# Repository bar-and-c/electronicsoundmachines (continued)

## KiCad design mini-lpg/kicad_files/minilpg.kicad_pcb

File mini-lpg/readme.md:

# Mini-LPG

General disclaimer: I have never used a real LPG, but I understand it is a bit more complex than this circuit. The control mechanism, as I understand it, is similar, though – using an optocoupler (often called Vactrol, after a common type). 

An optocoupler of this kind is an enclosed LED and a light dependent resistor (LDR): the more light from the LED, the lower the resistance. So, in this filter, the control voltage is used to make the LED shine, and the LDR is used in a simple low pass filter circuit. Voila – a simple voltage controlled filter. 

In revision A of this circuit I added (almost) as many extra add-ons I could think of – and left room for further, not yet thought of, modifications. In hindsight, I think I could have held back a bit: the distortion is weak (to my defence, it sounded much better on the breadboard – no idea what changed from that), possibly depending on what kind of signal you put through it; the band pass mode is not useless, but not extremely useful as it cuts a _lot_ of low end; the mod area and jumpers are a good idea in general, but on this particular device, maybe not... 

Annoyingly enough, one of the things I thought of but didn't include, a capacitor in series with the CV input to get a decay (given a gate signal as input), is something I have on similar cicuits and find really useful when lacking envelope generators. So I should have included that and omitted other stuff. Well well.

Most importantly, though: for some reason, the range is surprisingly narrow. Theorethically I had imagined that 0-12 volts would result in a filter going from completely silent to wide open, but in reality, the effective CV range is about 1.4 - 2.0 volts, or so. I don't know why. Could be that particular type of optocoupler, or something in the rest of my (mostly home built) synthesizer, or something in the overall design of the circuit, but there you go. 

So, that is good to know if you are considering building this. 

Having said that, I still think it brings a bit of value, at least if you have a tiny tiny modular like I do (at the time of building this, I have three oscillators, an eight step sequencer, a mixer module with two mixers in it, and two other passive LPGs similar to this one).

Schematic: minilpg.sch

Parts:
C1: 22nF; C_Rect_L7.2mm_W2.5mm_P5.00mm_FKS2_FKP2_MKS2_MKP2
D1: LED; LED_D3.0mm
D2: 1N4148; D_DO-35_SOD27_P7.62mm_Horizontal
D3: BAT43; D_DO-35_SOD27_P7.62mm_Horizontal
J1: CV; Switchcraft_35RAPC2AV_3_5_mm_jack
J2: IN; Switchcraft_35RAPC2AV_3_5_mm_jack
J3: OUT; Switchcraft_35RAPC2AV_3_5_mm_jack
JP1: MOD_CV; Pin_Header_Straight_1x02_Pitch2.54mm
JP2: MOD_IN; Pin_Header_Straight_1x02_Pitch2.54mm
JP3: MOD_MID; Pin_Header_Straight_1x02_Pitch2.54mm
JP4: MOD_OUT; Pin_Header_Straight_1x02_Pitch2.54mm
L1: 47mH; L_Radial_D12.0mm_P5.00mm_Fastron_11P
R1: 470; R_Axial_DIN0207_L6.3mm_D2.5mm_P7.62mm_Horizontal
R2: 270; R_Axial_DIN0207_L6.3mm_D2.5mm_P7.62mm_Horizontal
R3: 10k; R_Axial_DIN0207_L6.3mm_D2.5mm_P7.62mm_Horizontal
RV1: 50k; Potentiometer_Alps_RK09K_Horizontal
SW1: LP/BP; Switch-SPDT-angled
SW2: LPG/VCA; Switch-SPDT-angled
SW3: MINIDIST; Switch-SPDT-angled
U1: NSL-32; Optoisolator_NSL-32

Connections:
GND: D1.1, D2.2, J1.2, J2.2, J3.2, SW2.2 (B), SW3.2 (B), U1.2 (K)
unnamed: C1.1, D3.1 (K), JP3.2, JP4.1, L1.1, R3.2
unnamed: C1.2, SW1.2 (B), SW2.1 (A)
unnamed: D1.2, R1.1
unnamed: D2.1, R2.1, U1.1 (A)
unnamed: D3.2 (A), SW3.3 (C)
unnamed: J1.1, JP1.1, R1.2
unnamed: J2.1, JP2.2
unnamed: J3.1, JP4.2
unnamed: JP1.2, R2.2
unnamed: JP2.1, RV1.2, RV1.3
unnamed: JP3.1, U1.3 (R)
unnamed: L1.2, SW1.3 (C)
unnamed: R3.1, SW2.3 (C)
unnamed: RV1.1, U1.4 (R)

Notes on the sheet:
NOTE: The resistor values on the CV side are chosen to match the LEDs in the kit; 40 mA for the optocoupler and 20 mA for the LED. If you change these components, make sure the resistors match. Similarly, the components on the audio side are chosen to work OK with the optocoupler I chose (it has 50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
MODS: - The dist connaisseur mod: put a diode (Schottky or Germanium, since those have lower voltage drop => less loss) directly after the audio in jack, for another type of dist. - The filter mod: Put another capacitor (of significantly higher (or lower) value) instead of the VCA resistor (R3), fo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
Mini LPG
Mini LPG
September 8, 2018

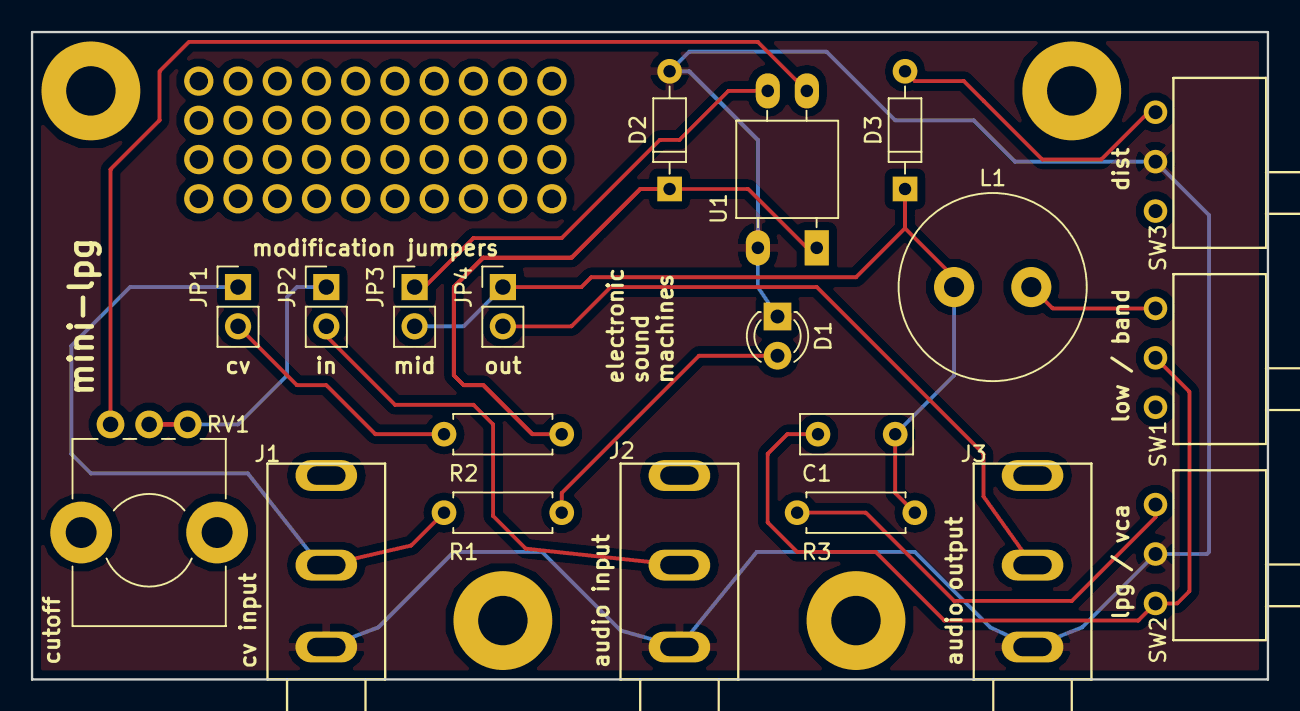
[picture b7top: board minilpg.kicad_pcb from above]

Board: 2 copper layers, 80.0 x 41.9 mm, 20 parts (0 on the bottom side), 15 nets.

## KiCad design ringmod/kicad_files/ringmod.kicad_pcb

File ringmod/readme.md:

# Ring modulator

This is just a textbook example of a ring modulator (see Wikipedia for reference). Given two input signals, the input and the carrier, as I understand it the output is the sum and difference frequencies (in an ideal circuit the input frequencies should not be in the output at all). 

In a more non-mathematical language: given two inputs, the input and the carrier, the output can be a bit unpredictable and often rather disharmonic. It can be used to create bell like sounds, robotic voices, or even quite pleasant sounds (if the input frequencies are carefully selected). 

It is super easy to build, and easy to use as it requires no power supply, just two input signals (just not too low in amplitude, use a pre-amplifier if needed).

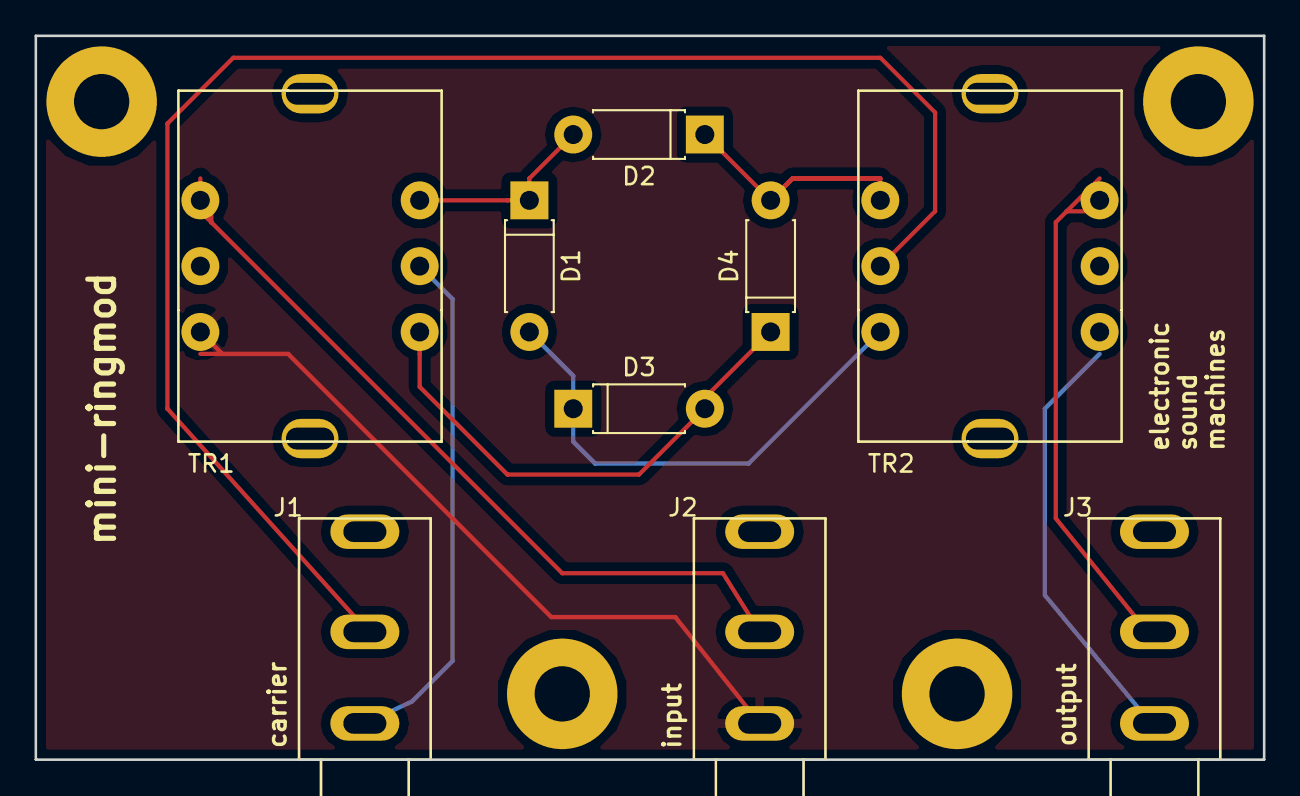
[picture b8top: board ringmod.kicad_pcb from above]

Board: 2 copper layers, 71.1 x 41.9 mm, 9 parts (0 on the bottom side), 10 nets.

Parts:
D1, D2, D3, D4: BAT43; D_DO-41_SOD81_P7.62mm_Horizontal
J1: CARRIER; Switchcraft_35RAPC2AV_3_5_mm_jack
J2: IN; Switchcraft_35RAPC2AV_3_5_mm_jack
J3: OUT; Switchcraft_35RAPC2AV_3_5_mm_jack
TR1, TR2: 42TM018; Transformer-42TM018

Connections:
unnamed: D1.1, D2.2, TR1.6
unnamed: D1.2, D3.1, TR2.3
unnamed: D2.1, D4.2, TR2.1
unnamed: D3.2, D4.1, TR1.4
unnamed: J1.1, TR2.2
unnamed: J1.2, TR1.5
unnamed: J2.1, TR1.1
unnamed: J2.2, TR1.3
unnamed: J3.1, TR2.6
unnamed: J3.2, TR2.4

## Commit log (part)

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2018-02-21 Add initial Jekyll site
2018-02-21 The first version with some content
2018-02-21 Add layout from minima theme, to override
    And overriding a bit already.
2018-02-21 Make image smaller
2018-02-22 Add Gemfile.lock to repo
2018-02-22 Add minima assets in feeble attempt to make it work
2018-02-22 Copy stuff from working jekyll site
2018-02-22 clean up config
2018-02-22 Add a lot of info, and enhanced image
2018-02-22 Remove repetitive phrase
2018-02-22 Remove typo in URL
    Trying to get the form in English. Good luck with that!
2018-02-22 Adjust the image text a tad south
2018-02-23 Add and reorganize content
2018-02-23 Add more on learning
2018-02-23 Update about language
2018-02-23 Changed wording
2018-02-23 Express that spending time on experiments is not mandatory
2018-02-26 Change name from 'guitar' to 'effect'
2018-03-14 Update with info about gender balance
2018-03-14 Add more info on gender balance, removing Google Form
2018-03-16 Add initial documentation
    Still a long way to go, with adding schematics, and maybe photos.
2018-03-16 Add custom library with power pins
    4017 and 40106 didn't have explicit power pins, which drove me insane,
    so I made my own copies.
    4017 has its old pins, but no longer invisible, and 40106 has a new
    part (G) that holds power pins.
    Help: https://www.youtube.com/watch?v=-1WVtuzKmz8
2018-03-16 Add schematic as PDF, rev A
2018-03-16 Update schematic with new components
    Replace annoying ones with hidden power with my copies that
    have power. So.
2018-03-17 Add first attempt towards PCB layout of SSS-1
    Well, it's a start...
    Inspiration and help from e.g.:
    http://www.xess.com/blog/my-first-kicad-board/
    and obviously Contextual Electronics' YouTube tutorials, mainly
    various bits of the "Getting To Blinky" series.
2018-03-17 Add schematic for General Fukup crossover dist
    I distortion pedal I built in July 2017.
2018-03-18 Add 2P5T switch
2018-04-30 Add almost finished Metallic Beat (CR-78)
2018-04-30 Add Thomas Henry's VCO-1
    Revision A, ordered April 30, 2018.
2018-05-01 Add page about synth project (Minimodi)
    Also added snippets about KiCad, not much there yet, though.
2018-05-01 Add links to Thomas Henry stuff
2018-05-01 Add a bit about keyboard
2018-05-02 More on keyboard
2018-05-02 More on envelopes
2018-05-28 Changed resistor values to 12 V
    Changed most of the resistors mentioned in these threads:
    http://www.electro-music.com/forum/topic-54360.html
    http://electro-music.com/forum/topic-36820.html
    Not yet changed R23 or R41, in the original schematics. Will do
    that after trying it in real life.
    Also maybe R46, for fine tuning to span one octave.
2018-06-04 Add passive vactrol low pass filter
    Maybe "LPG" is the wrong word, I don't really know what that word contains.
    But it is vactrol based, like an LPG.
    Inspiration taken from various forums, etc.
2018-06-04 Add schematic PDF and readme for Metallic Beat
2018-06-09 Update PCB with initial 12 V values
    And add PCB layout pdf.
2018-06-09 Add panel design resources
    Will see how it pans out, but the intention is to use these for
    laser cutting panels.
    PNGs found on Reddit (thank you!):
    https://www.reddit.com/r/modular/comments/310nyb/eurorack_pcb_and_panel_dimensions_for_4hp_8hp_and/
    Also added InkScape template for 8HP.
2018-07-12 Add panel draft for VCO-1
    NOTE: There are hidden layers that can mess up the laser cutting
    software (it did for me).
    NOTE: The pots in PCB rev A (and probably rev B as well) will have
    reversed rotation if mounted as the PCB suggests. In the future I
    will mount the pots on the other side (if not fixing the PCB), and
    in that case, the panel must be changed (swap the columns of holes).
2018-07-12 Update after rev A failure
    Fixed most of the errors found in rev A. No fix for the
    reverse pots, though, since I don't know how.
    At this point it would also mean to re-CAD, not too happy
    about that.
2018-07-12 Use 16 pole power connector
    Even though a 10 pole would be enough, my current plan is
    to use 16 pole for all boards, thus minimizing cost for
    power connectors/cables.
    Possibly a bad idea, but if I will go through with the plans
    to run workshops using these boards, there will be a LOT of
    component bought, and it makes sense to keep cost down.
2018-07-18 Add symbol for CEM3340
2018-07-21 Add schematic for CEM3340 based VCO
2018-07-21 Add Gerber files for Pro-3340 rev A
2018-08-09 Update SSS-1 to beyond prototype
    Adding features after using the stripboard prototype a bit, like e.g.:
    - Searate output for all steps.
    - Using 12V logic (will probably use the small connector for all PCBs).
    - Switch for hold/run.
    - Switch for step.
    - Switch for reset.
2018-08-09 Add draft for AS3320 VCF
    Still quite unfinished (not even on breadboard yet), but most
    stuff theorethically in place. :-)
    Also added AS3320 and 3PDT switch to lib.
2018-08-09 Update docs with...stuff, e.g. add Punk Modular
    A misc kind of commit. Just added stuff, ramblings, findings,
    about the tiny "minimodi" synth, about links to info and learning
    about KiCad, but also about another workshop idea, "Punk Modular".
    My "ideal" building kit would be a finished synth. Like MiniModi.
    But, since it is a complete kit it takes a LOT of design, choices
    to make, decisions -- while building a modular is quite easy by
2018-08-20 Finish (kind of) 3320 VCF
    OK, it's not finished as such, nothing is tested at this point.
    But the schematic is complete as far as I can tell without having
    tested it. :-)
2018-08-20 Switch panel columns
    Since the PCB (rev A, at least) has its pots in a way
    I didn't expect, the old layout of the panel made the
    pots work "backwards".
    Swapping the columns so that the pots can be mounted
    on the other side of the PCB.
2018-08-20 pro3340: Add BOM, panel, and PCB png
    The panel is not tested with PCB, and the BOM is not really
    reviewed. E.g. I know it could use better info on the frequency
    capacitor (type of capacitor), and the sync switch (it's some odd
    kind of three way switch), at least. Also, sockets are not included
    (not required, obviously, but might note it so that one doesn't
    forget about it).
2018-08-26 Add 4xVCA schematic – based on V2164 IC
    Just the reference implementation, basically, with a few tweaks.
    Also added the component to the KiCad library.
2018-08-30 Add untested draft of slew/rhythm kind of thing
    Meant to be three lines of slew limiters, generating delayed
    signals, that are chained together.
2018-09-08 Add unfinished 3310 ADSR, mixer, PSU, ringmod, mini-LPG, and VCA-1
2018-09-08 Add logo files (completely unordered)
2018-09-09 Ringmod and minimod layout done
2018-09-10 Change transformer footprint after test
2018-09-11 Final touches to ringmod/LPG PCB for rev A
2018-10-02 Update ringmod to KiCad 5 (and minor updates)
    Updating to KiCad 5. Not sure which files that are important,
    so yeah.
    Also possibly minor updates in schematic (diode values), plus an
    image of a built prototype and a pdf of the schematic.
2018-10-02 Update ringmod to KiCad 5 (and minor updates)
    Updating to KiCad 5. Not sure which files that are important,
    so yeah.
    Also minor updates in schematic (diode and resistor values,and
    documentation text), plus an image of a built prototype and a
    pdf of the schematic.
2018-10-02 Add .gitignore
2018-10-06 Brush up docs on ringmod and mini-LPG
2018-10-07 Add info on ringmod workshop
2018-10-09 Add pictures to ringmod workshop docs
2019-01-25 Lots of changes, not sure what is what
2019-01-26 Add coil jumper on DR-77/78
2019-01-26 Add trig capacitor jumper on Metallic Beat
2019-01-26 Add coil footprint, update DR-77/78
2019-01-27 Convert 4xVCA to KiCad5
2019-02-05 First revision of DR-77/78 PCB
2019-02-19 Polish up the DR-77/78 schematic
2019-04-06 Add footprint for Electrokit slide switch
    Adding footprints for DPDT slide switch, so that it can be used
    as SPDT and SPST as well.
    https://www.electrokit.com/en/product/slide-switch-2-p-on-on-solder-lugs-3/
    Part.no: 41011900
2019-04-09 Clean up, and finish PCB
    Removing the worst of the switch excesses (or adding a few switches,
    depending on what was in the last commit).
2019-04-09 Moved 3320 VCF to KiCad5 -- NOT VERIFIED
    There seem to be a lot of errors with the switches.
    Considering replacing them with either jumpers, or possibly
    cheaper DPDT push switches (using two for the 3PDT cases, hoping
    it won't fry anything).
    Still, this commit is just a level up to KiCad 5, no functional
    changes done yet. A few will follow.
2019-04-13 pro3320: Start working on PCB
2019-04-14 pro3320: Abandon panel PCB
    I tried having a PCB parallell to the panel, but it gets too
    wide for my taste (and/or requires too much time and brain
    activity in the PCB layout tool).
    Will slim it down, having the PCB hanging on the pots, and
    mounting the jacks on panel, the switches as well, having
    to solder a LOT of cables. It will be hell, but I don't see
2019-04-14 kicadlib: Fix pins for 3PDT
2019-04-14 kicadlib.pretty: Add 17x7 mod area
2019-04-14 pro3320: First messy PCB attempt
2019-04-15 Add 16x7 mod area
2019-04-16 pro3320: Finish PCB routing
    It's not pretty, but will hopefully work.
    There is something missing in my layout knowledge,I believe;
    it feels like a better layout would make routing easier.
    Whatevs.
2019-04-16 Add Electronic Sound Machines logo (996x49)
2019-04-16 pro3320: Add logo to PCB
    Also, polishing the PCB and schematic a wee bit.
    Faced with the choice, what would you say?
2019-04-16 Add Electronic Sound Machines logo in other sizes
2019-04-19 footprints: Add non switching Switchcraft jack
2019-04-19 metallic beat: Finish PCB layout and routing
2019-04-21 metallic beat: Add jumper for VCA
    Mainly for test and experimentation purposes, having a jumper in
    the oscillator signal's path to the VCA/filter thing could be nice
    to make it possible to run other things through there.
    NOTE: When building,one will have to add a capacitor on the jack!
    I figured the existing one would be too small to use as a
    decoupling capacitor.
2019-04-22 triggerhappy: Add schematic/layout (for delayed trig pulses)
    Also adding footprint for PJ301 jack w/o switch.
2019-04-22 pro3320: Fix wrong direction of pots
2019-04-22 triggerhappy: Add text
2019-04-25 Adding gerber files for boards
2019-05-05 Add panels for pro3320, triggerhappy, minidrum, metallic beat
2019-05-09 Stuff that was left on my old computer (KiCad 4)
2019-05-11 Clean up panels for laser printing
2019-05-12 Just notes in some schematics
2019-05-18 Add areas to make panel thinner (for holes)
2019-05-31 Bits and pieces on e.g. delays
2019-07-15 ringmod doc: Fix minor errors after review
2019-07-15 Change focus to modular stuff, also adding minidrum
2019-07-15 Change title of minidrum page and increase base font
2019-08-25 pro3320: Update docs and some component values
2019-08-25 pro3320: Update schematic comments and add PDF
    NOTE: Also adding BOM, but since so much is whacky in the scematic,
    don't count on it being correct.
2020-09-28 Add info on my minidrum implementation, my values
2020-09-28 Add some components (a jack?)
2020-09-28 Unknown changes in 4xVCA (yes, unknown)
2020-09-28 Add unknown project, 'distamp'
    YES, unknown! I am not perfect. I am imperfect.
2020-09-28 Add another unknown project, 'passive glide decay'
    Probably the crude LP/HP thing I did soldered on switches and jacks.
2020-09-28 Add working skeleton of lil drummer
    A simple tap-tempo-drummachine-sync thing.
    Tap one-two-three-four-one, and on the last "one" the sync starts.
    A one man band tool.
2020-09-28 Rewrite with classes (with Linux dev support)
    Split stuff up in classes, not so much for the code's sake,
    but to make it easier to mock the I/O, for development purposes.
    So now it's possible to run in Linux, with mouse clicks as taps.
    The new main module is lildrum.py, keeping lil_drummer.py around
    for a while.
